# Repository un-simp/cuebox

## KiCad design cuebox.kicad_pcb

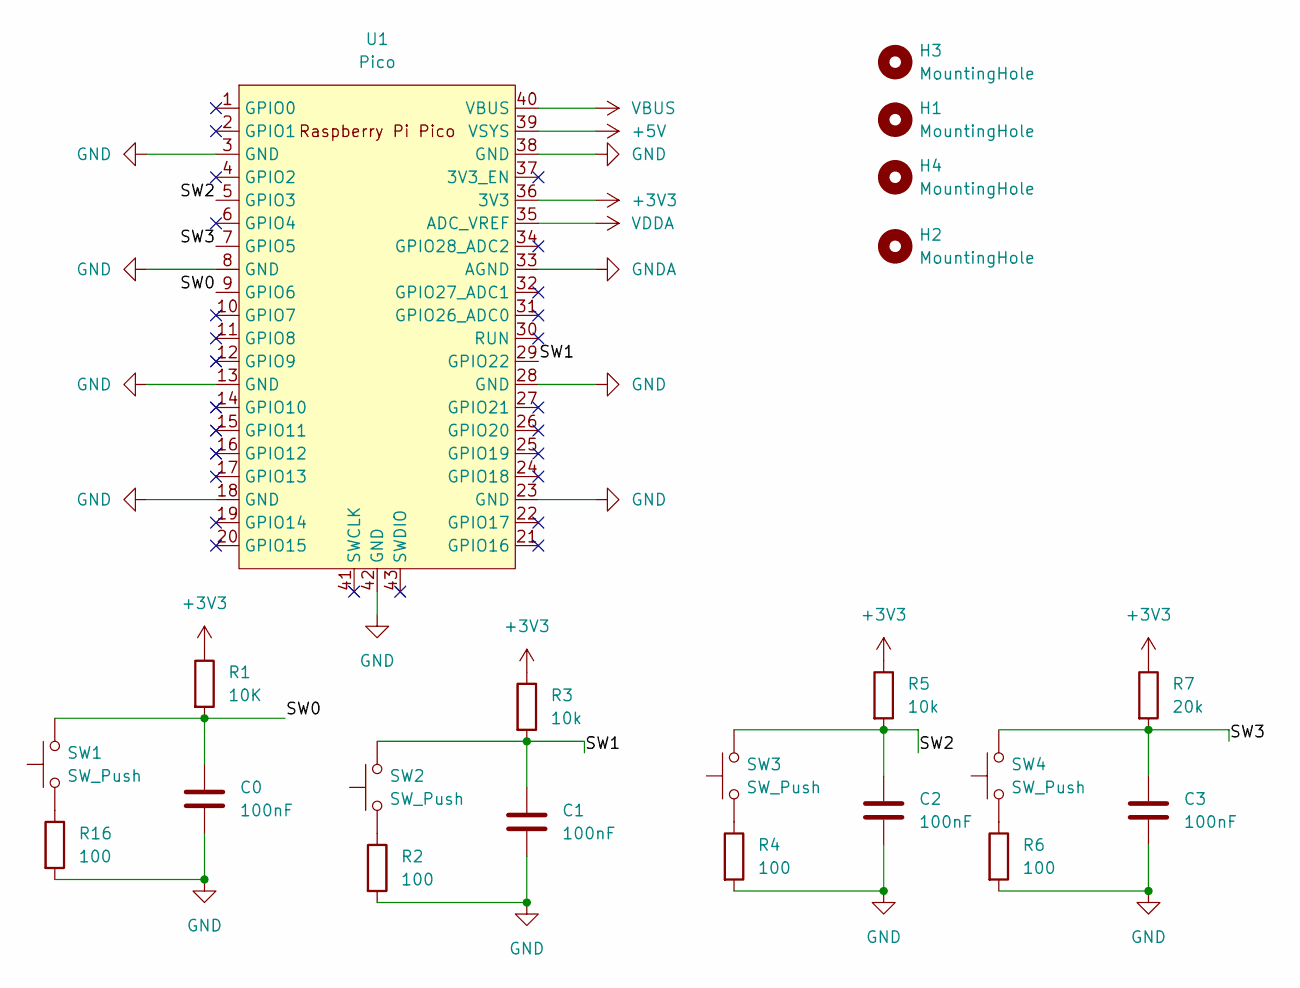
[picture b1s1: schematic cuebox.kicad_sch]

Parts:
C0, C1, C2, C3: 100nF; CP_Radial_D4.0mm_P1.50mm
H1, H2, H3, H4: MountingHole; MountingHole_3mm_Pad
R1: 10K; R_Axial_DIN0516_L15.5mm_D5.0mm_P5.08mm_Vertical
R2, R4, R6, R16: 100; R_Axial_DIN0516_L15.5mm_D5.0mm_P5.08mm_Vertical
R3, R5: 10k; R_Axial_DIN0516_L15.5mm_D5.0mm_P5.08mm_Vertical
R7: 20k; R_Axial_DIN0516_L15.5mm_D5.0mm_P5.08mm_Vertical
SW1, SW2, SW3, SW4: SW_Push; SW_PUSH_6mm_H5mm
U1: Pico; RPi_Pico_SMD_TH

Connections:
+3V3: R1.1, R3.1, R5.1, R7.1, U1.36 (3V3)
+5V: U1.39 (VSYS)
/SW0: C0.1, R1.2, SW1.2, U1.9 (GPIO6)
/SW1: C1.1, R3.2, SW2.2, U1.29 (GPIO22)
/SW2: C2.1, R5.2, SW3.2, U1.5 (GPIO3)
/SW3: C3.1, R7.2, SW4.2, U1.7 (GPIO5)
GND: C0.2, C1.2, C2.2, C3.2, R2.2, R4.2, R6.2, R16.2, U1.3 (GND), U1.8 (GND), U1.13 (GND), U1.18 (GND), U1.23 (GND), U1.28 (GND), U1.38 (GND), U1.42 (GND)
GNDA: U1.33 (AGND)
unnamed: R2.1, SW2.1
unnamed: R4.1, SW3.1
unnamed: R6.1, SW4.1
unnamed: R16.1, SW1.1
VBUS: U1.40 (VBUS)
VDDA: U1.35 (ADC_VREF)

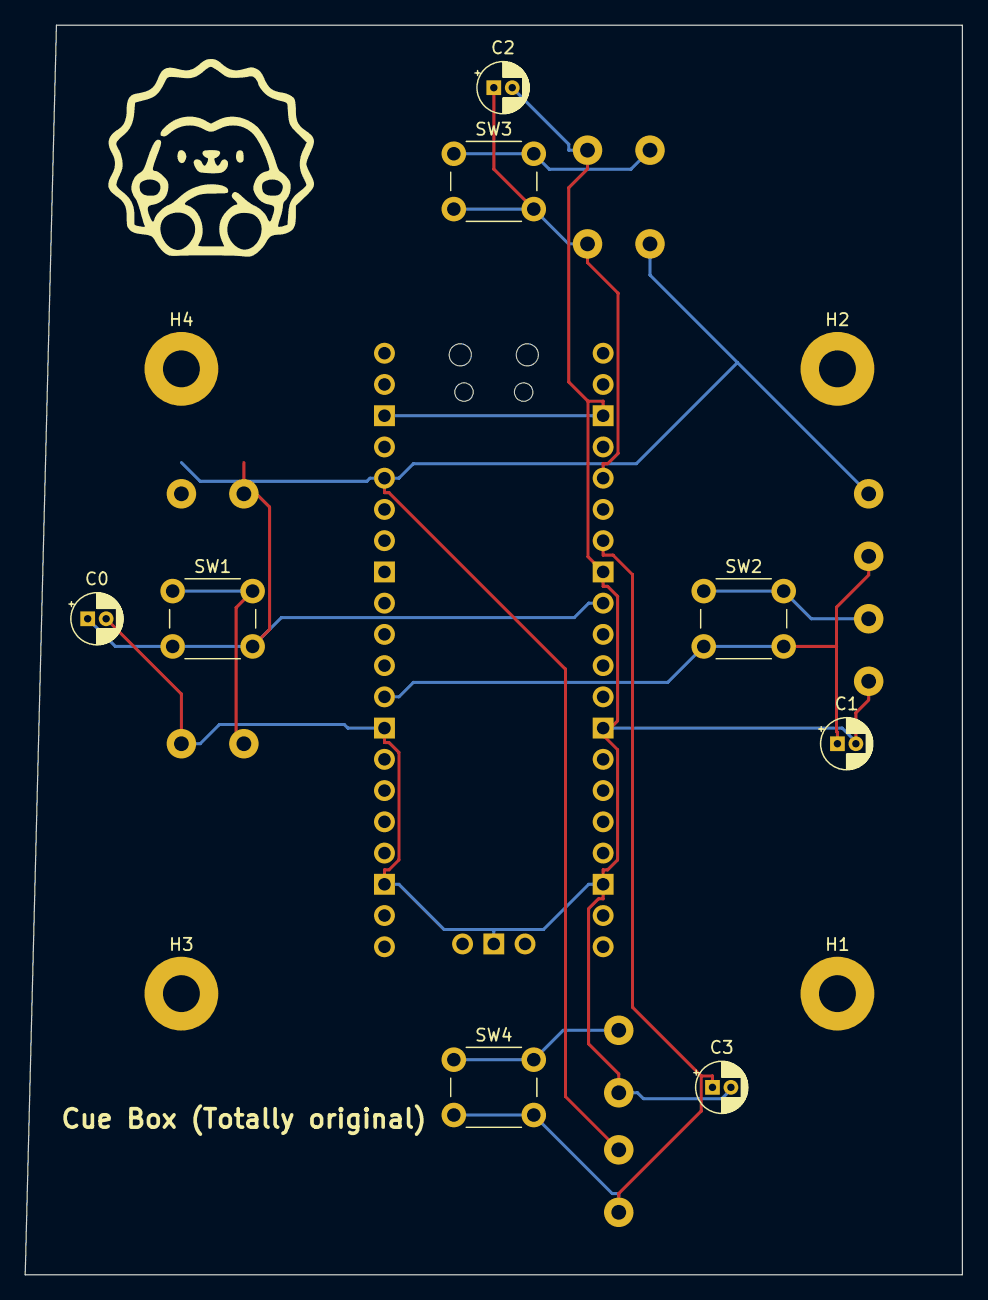
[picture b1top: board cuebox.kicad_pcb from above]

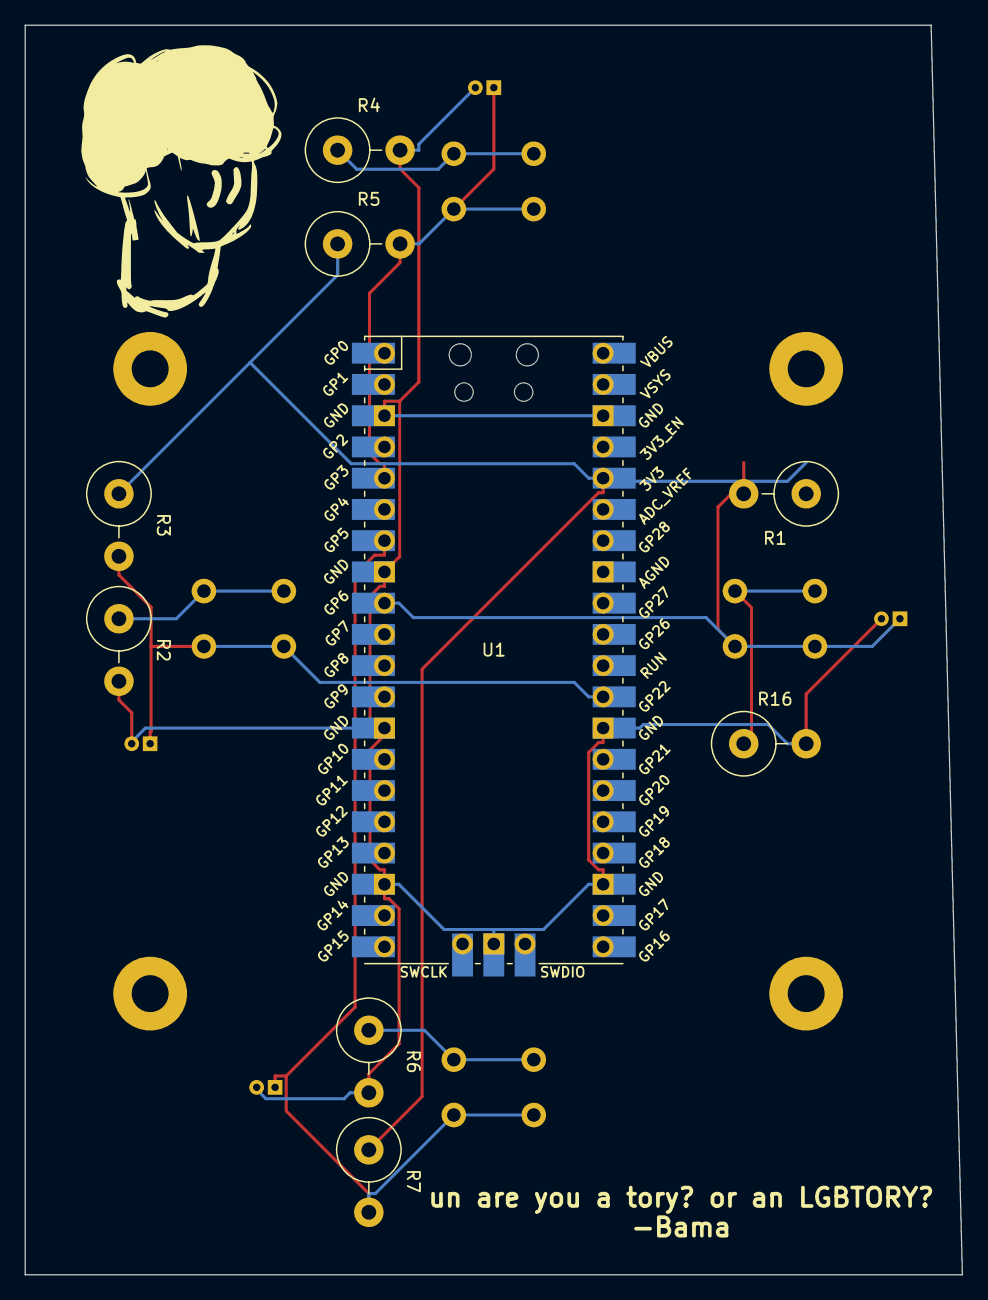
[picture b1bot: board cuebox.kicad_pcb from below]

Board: 2 copper layers, 76.2 x 101.6 mm, 21 parts (9 on the bottom side), 10 nets.

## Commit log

2022-11-20 added cpp gitignore
2022-11-20 init
